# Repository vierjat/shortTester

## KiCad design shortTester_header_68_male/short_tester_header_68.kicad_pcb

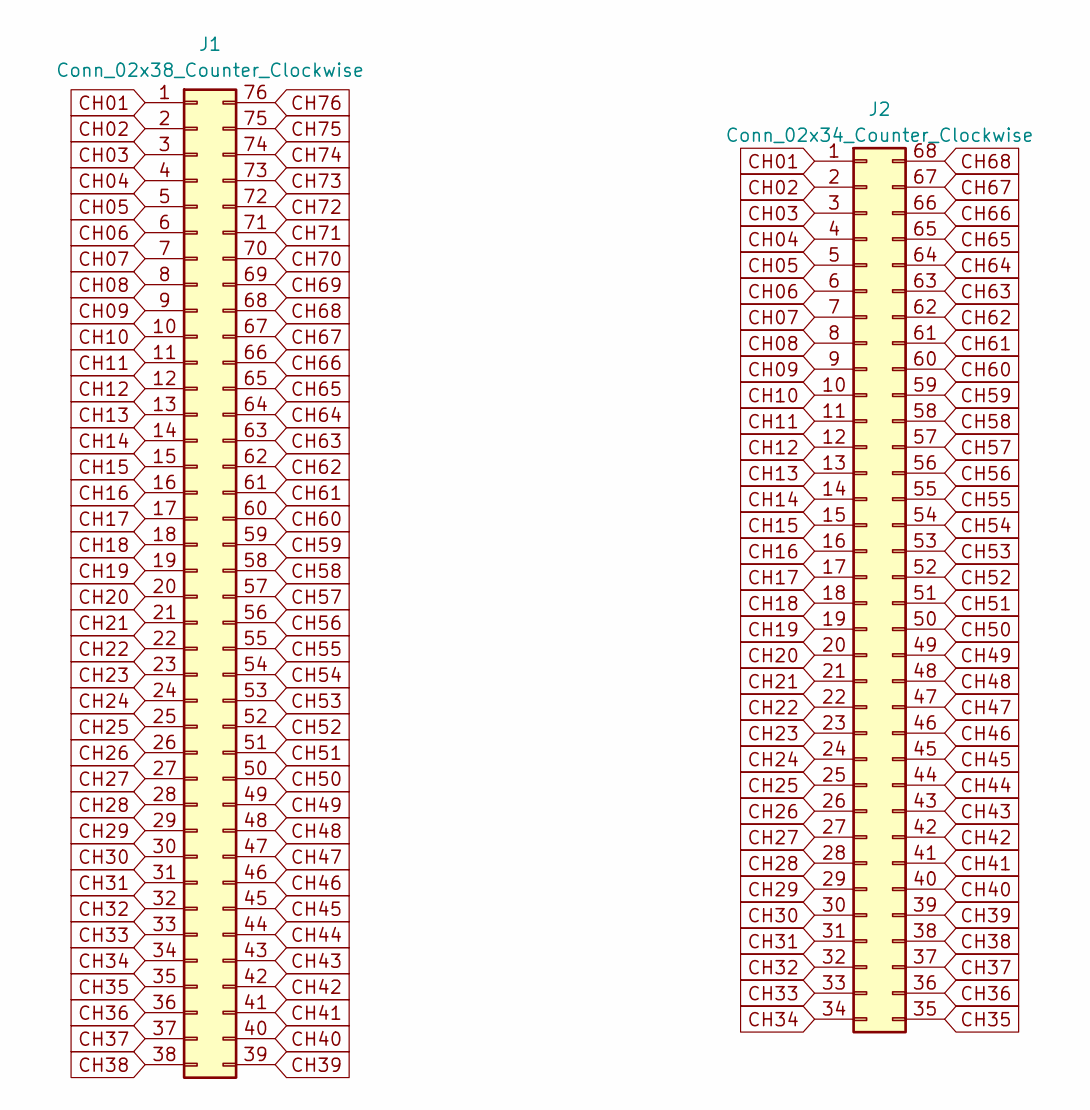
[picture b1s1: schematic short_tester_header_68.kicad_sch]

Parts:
J1: Conn_02x38_Counter_Clockwise; PinSocket_2x38_P2.54mm_Vertical
J2: Conn_02x34_Counter_Clockwise; 2-5174339-5_SSC_68pin-male

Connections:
CH01: J1.1, J2.1
CH02: J1.2, J2.2
CH03: J1.3, J2.3
CH04: J1.4, J2.4
CH05: J1.5, J2.5
CH06: J1.6, J2.6
CH07: J1.7, J2.7
CH08: J1.8, J2.8
CH09: J1.9, J2.9
CH10: J1.10, J2.10
CH11: J1.11, J2.11
CH12: J1.12, J2.12
CH13: J1.13, J2.13
CH14: J1.14, J2.14
CH15: J1.15, J2.15
CH16: J1.16, J2.16
CH17: J1.17, J2.17
CH18: J1.18, J2.18
CH19: J1.19, J2.19
CH20: J1.20, J2.20
CH21: J1.21, J2.21
CH22: J1.22, J2.22
CH23: J1.23, J2.23
CH24: J1.24, J2.24
CH25: J1.25, J2.25
CH26: J1.26, J2.26
CH27: J1.27, J2.27
CH28: J1.28, J2.28
CH29: J1.29, J2.29
CH30: J1.30, J2.30
CH31: J1.31, J2.31
CH32: J1.32, J2.32
CH33: J1.33, J2.33
CH34: J1.34, J2.34
CH35: J1.35, J2.35
CH36: J1.36, J2.36
CH37: J1.37, J2.37
CH38: J1.38, J2.38
CH39: J1.39, J2.39
CH40: J1.40, J2.40
CH41: J1.41, J2.41
CH42: J1.42, J2.42
CH43: J1.43, J2.43
CH44: J1.44, J2.44
CH45: J1.45, J2.45
CH46: J1.46, J2.46
CH47: J1.47, J2.47
CH48: J1.48, J2.48
CH49: J1.49, J2.49
CH50: J1.50, J2.50
CH51: J1.51, J2.51
CH52: J1.52, J2.52
CH53: J1.53, J2.53
CH54: J1.54, J2.54
CH55: J1.55, J2.55
CH56: J1.56, J2.56
CH57: J1.57, J2.57
CH58: J1.58, J2.58
CH59: J1.59, J2.59
CH60: J1.60, J2.60
CH61: J1.61, J2.61
CH62: J1.62, J2.62
CH63: J1.63, J2.63
CH64: J1.64, J2.64
CH65: J1.65, J2.65
CH66: J1.66, J2.66
CH67: J1.67, J2.67
CH68: J1.68, J2.68
CH69: J1.69
CH70: J1.70
CH71: J1.71
CH72: J1.72
CH73: J1.73
CH74: J1.74
CH75: J1.75
CH76: J1.76

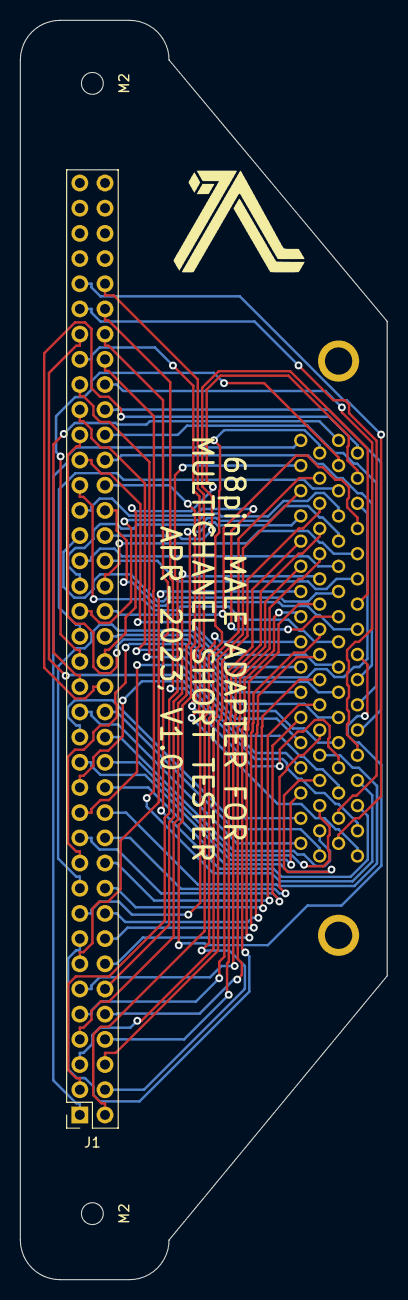
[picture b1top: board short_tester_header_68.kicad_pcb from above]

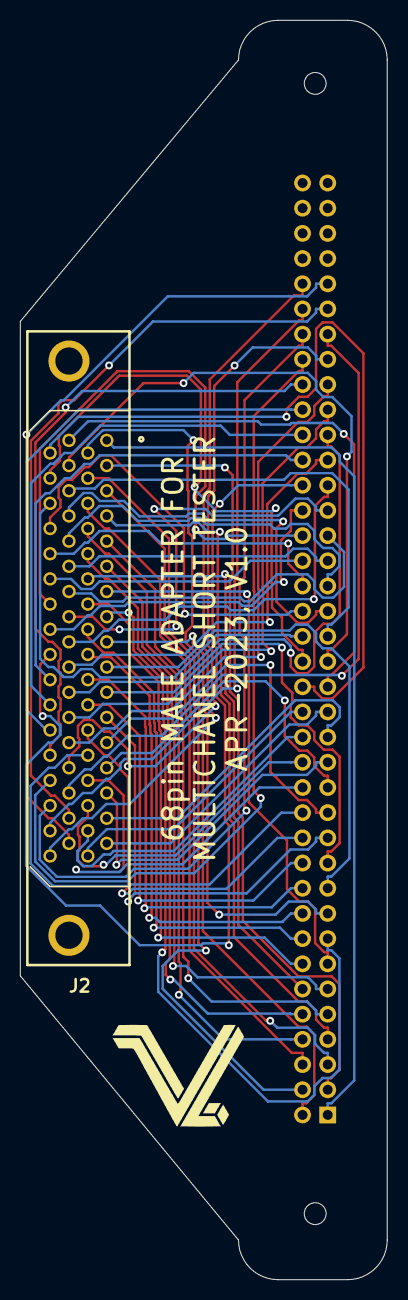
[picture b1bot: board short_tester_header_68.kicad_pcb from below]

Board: 2 copper layers, 37.0 x 127.0 mm, 6 parts (2 on the bottom side), 68 nets.

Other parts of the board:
G1, G2: LOGO; lamda15mm
M2, M2#2: MountingHole_2.2mm_M2

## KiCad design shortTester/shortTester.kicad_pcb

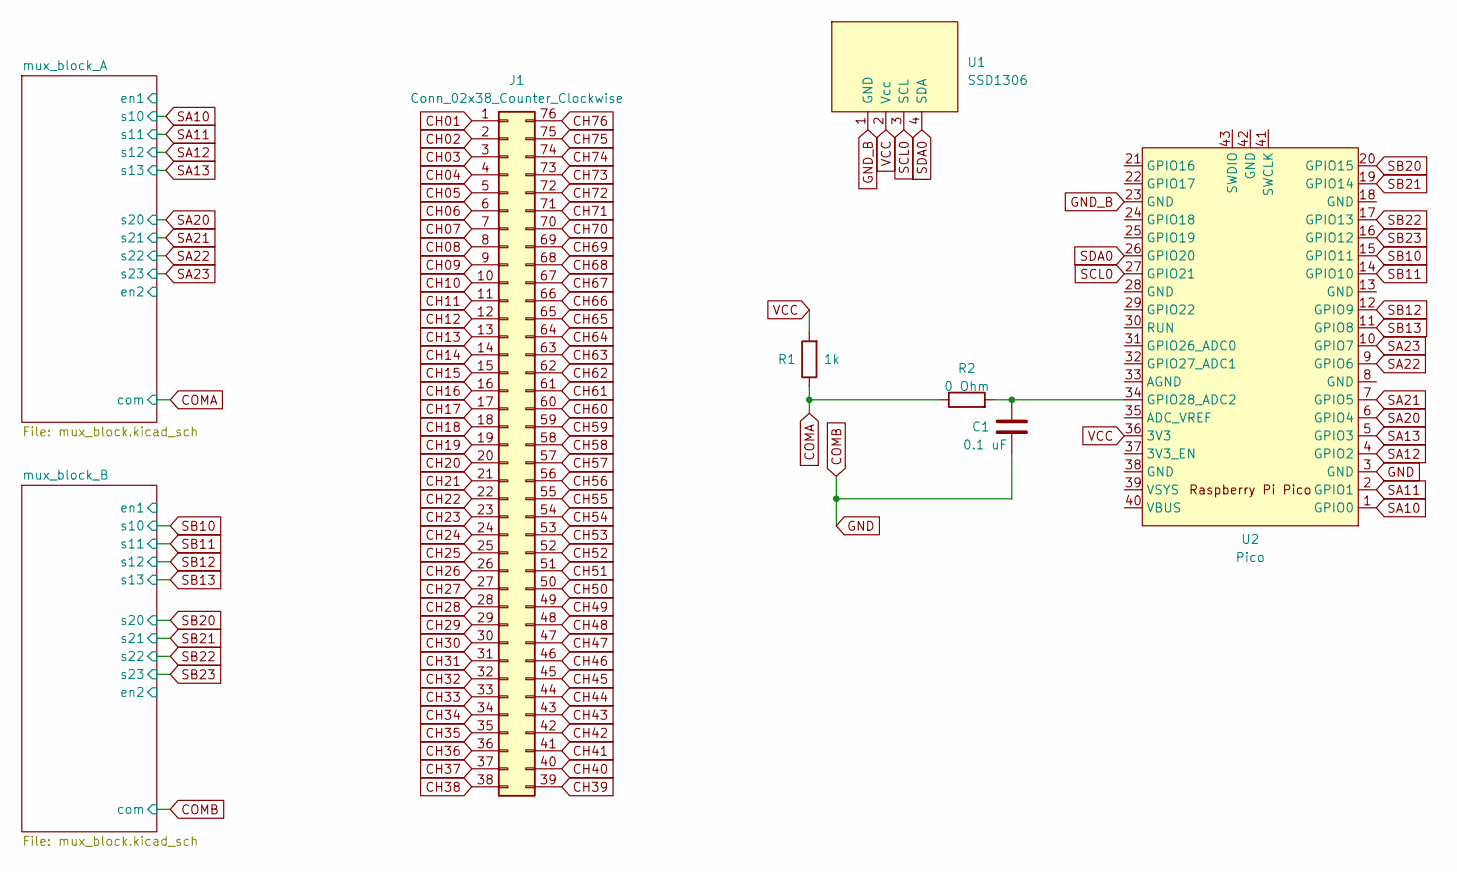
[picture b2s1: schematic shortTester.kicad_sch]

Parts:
C1: 0.1 uF; C_1210_3225Metric_Pad1.33x2.70mm_HandSolder
J1: Conn_02x38_Counter_Clockwise; PinHeader_2x38_P2.54mm_Vertical
R1: 1k; R_1210_3225Metric_Pad1.30x2.65mm_HandSolder
R2: 0 Ohm; R_1210_3225Metric_Pad1.30x2.65mm_HandSolder
U1: SSD1306
U2: Pico; RPi_Pico_SMD_TH

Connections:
CH01: J1.1; also elsewhere on the board
CH02: J1.2; also elsewhere on the board
CH03: J1.3; also elsewhere on the board
CH04: J1.4; also elsewhere on the board
CH05: J1.5; also elsewhere on the board
CH06: J1.6; also elsewhere on the board
CH07: J1.7; also elsewhere on the board
CH08: J1.8; also elsewhere on the board
CH09: J1.9; also elsewhere on the board
CH10: J1.10; also elsewhere on the board
CH11: J1.11; also elsewhere on the board
CH12: J1.12; also elsewhere on the board
CH13: J1.13; also elsewhere on the board
CH14: J1.14; also elsewhere on the board
CH15: J1.15; also elsewhere on the board
CH16: J1.16; also elsewhere on the board
CH17: J1.17; also elsewhere on the board
CH18: J1.18; also elsewhere on the board
CH19: J1.19; also elsewhere on the board
CH20: J1.20; also elsewhere on the board
CH21: J1.21; also elsewhere on the board
CH22: J1.22; also elsewhere on the board
CH23: J1.23; also elsewhere on the board
CH24: J1.24; also elsewhere on the board
CH25: J1.25; also elsewhere on the board
CH26: J1.26; also elsewhere on the board
CH27: J1.27; also elsewhere on the board
CH28: J1.28; also elsewhere on the board
CH29: J1.29; also elsewhere on the board
CH30: J1.30; also elsewhere on the board
CH31: J1.31; also elsewhere on the board
CH32: J1.32; also elsewhere on the board
CH33: J1.33; also elsewhere on the board
CH34: J1.34; also elsewhere on the board
CH35: J1.35; also elsewhere on the board
CH36: J1.36; also elsewhere on the board
CH37: J1.37; also elsewhere on the board
CH38: J1.38; also elsewhere on the board
CH39: J1.39; also elsewhere on the board
CH40: J1.40; also elsewhere on the board
CH41: J1.41; also elsewhere on the board
CH42: J1.42; also elsewhere on the board
CH43: J1.43; also elsewhere on the board
CH44: J1.44; also elsewhere on the board
CH45: J1.45; also elsewhere on the board
CH46: J1.46; also elsewhere on the board
CH47: J1.47; also elsewhere on the board
CH48: J1.48; also elsewhere on the board
CH49: J1.49; also elsewhere on the board
CH50: J1.50; also elsewhere on the board
CH51: J1.51; also elsewhere on the board
CH52: J1.52; also elsewhere on the board
CH53: J1.53; also elsewhere on the board
CH54: J1.54; also elsewhere on the board
CH55: J1.55; also elsewhere on the board
CH56: J1.56; also elsewhere on the board
CH57: J1.57; also elsewhere on the board
CH58: J1.58; also elsewhere on the board
CH59: J1.59; also elsewhere on the board
CH60: J1.60; also elsewhere on the board
CH61: J1.61; also elsewhere on the board
CH62: J1.62; also elsewhere on the board
CH63: J1.63; also elsewhere on the board
CH64: J1.64; also elsewhere on the board
CH65: J1.65; also elsewhere on the board
CH66: J1.66; also elsewhere on the board
CH67: J1.67; also elsewhere on the board
CH68: J1.68; also elsewhere on the board
CH69: J1.69; also elsewhere on the board
CH70: J1.70; also elsewhere on the board
CH71: J1.71; also elsewhere on the board
CH72: J1.72; also elsewhere on the board
CH73: J1.73; also elsewhere on the board
CH74: J1.74; also elsewhere on the board
CH75: J1.75; also elsewhere on the board
CH76: J1.76; also elsewhere on the board
COMA: R1.1, R2.1; also elsewhere on the board
COMB: C1.2, U2.3 (GND); also elsewhere on the board
GND_B: U1.1 (GND), U2.23 (GND)
unnamed: C1.1, R2.2, U2.34 (GPIO28_ADC2)
SA10: U2.1 (GPIO0); also elsewhere on the board
SA11: U2.2 (GPIO1); also elsewhere on the board
SA12: U2.4 (GPIO2); also elsewhere on the board
SA13: U2.5 (GPIO3); also elsewhere on the board
SA20: U2.6 (GPIO4); also elsewhere on the board
SA21: U2.7 (GPIO5); also elsewhere on the board
SA22: U2.9 (GPIO6); also elsewhere on the board
SA23: U2.10 (GPIO7); also elsewhere on the board
SB10: U2.15 (GPIO11); also elsewhere on the board
SB11: U2.14 (GPIO10); also elsewhere on the board
SB12: U2.12 (GPIO9); also elsewhere on the board
SB13: U2.11 (GPIO8); also elsewhere on the board
SB20: U2.20 (GPIO15); also elsewhere on the board
SB21: U2.19 (GPIO14); also elsewhere on the board
SB22: U2.17 (GPIO13); also elsewhere on the board
SB23: U2.16 (GPIO12); also elsewhere on the board
SCL0: U1.3 (SCL), U2.27 (GPIO21)
SDA0: U1.4 (SDA), U2.26 (GPIO20)
VCC: R1.2, U1.2 (Vcc), U2.36 (3V3); also elsewhere on the board

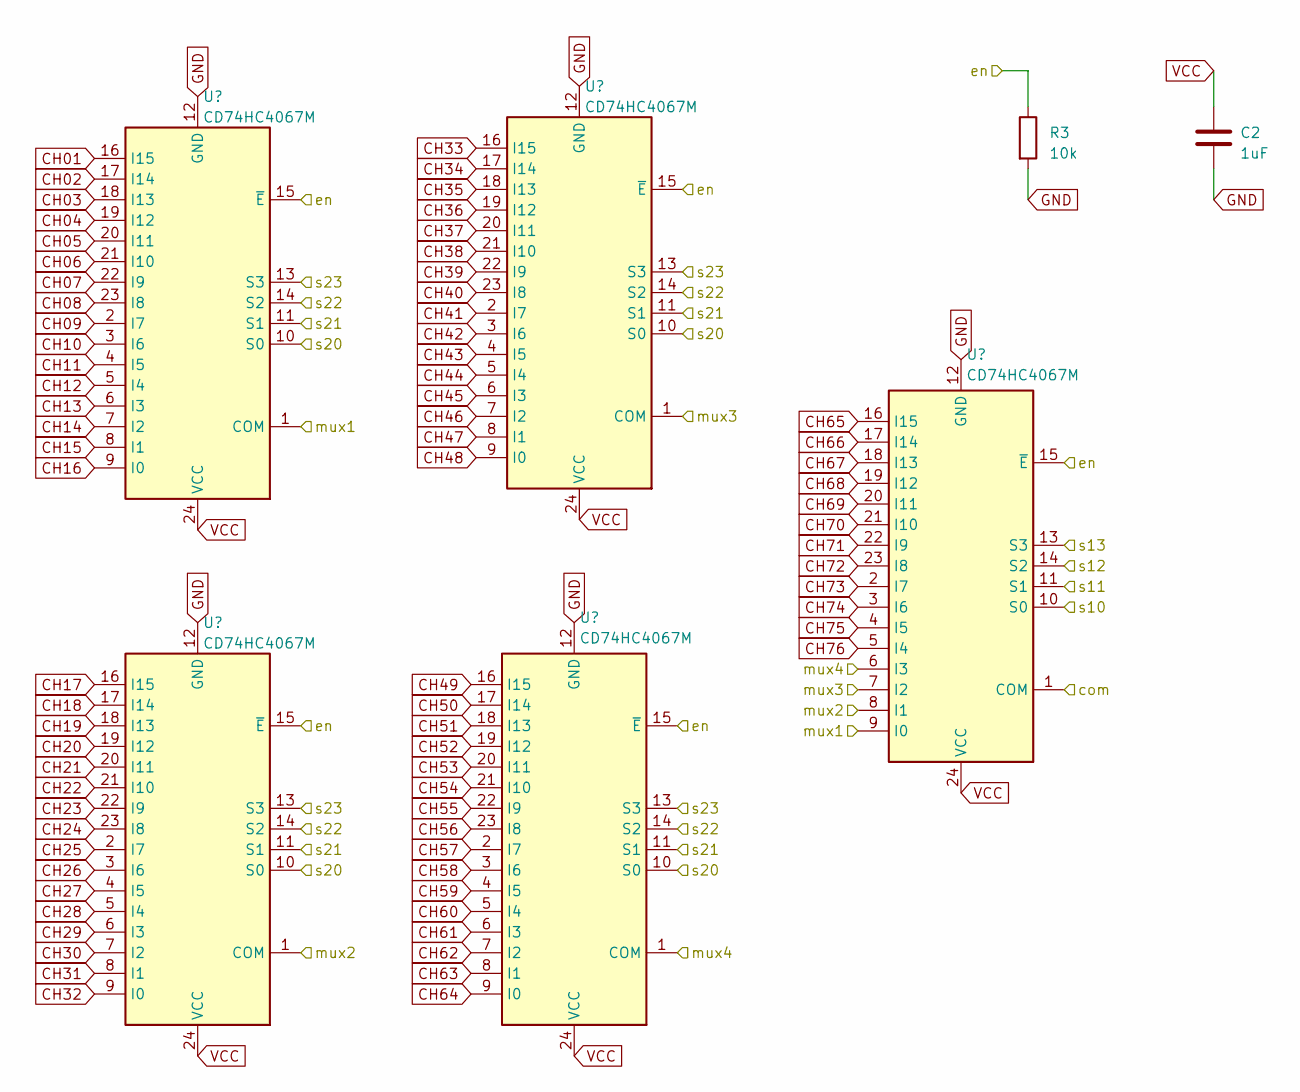
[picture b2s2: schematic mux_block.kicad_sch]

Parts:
C2: 1uF; C_1206_3216Metric_Pad1.33x1.80mm_HandSolder
R3: 10k; R_1210_3225Metric_Pad1.30x2.65mm_HandSolder
U3, U4, U5, U6, U7: CD74HC4067M; SOIC-24W_7.5x15.4mm_P1.27mm

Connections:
/mux_block_A/en: R3.1, U3.15 (~E), U4.15 (~E), U5.15 (~E), U6.15 (~E), U7.15 (~E)
/mux_block_A/mux1: U3.1 (COM), U7.9 (I0)
/mux_block_A/mux2: U4.1 (COM), U7.8 (I1)
/mux_block_A/mux3: U6.1 (COM), U7.7 (I2)
/mux_block_A/mux4: U5.1 (COM), U7.6 (I3)
CH01: U3.16 (I15); also elsewhere on the board
CH02: U3.17 (I14); also elsewhere on the board
CH03: U3.18 (I13); also elsewhere on the board
CH04: U3.19 (I12); also elsewhere on the board
CH05: U3.20 (I11); also elsewhere on the board
CH06: U3.21 (I10); also elsewhere on the board
CH07: U3.22 (I9); also elsewhere on the board
CH08: U3.23 (I8); also elsewhere on the board
CH09: U3.2 (I7); also elsewhere on the board
CH10: U3.3 (I6); also elsewhere on the board
CH11: U3.4 (I5); also elsewhere on the board
CH12: U3.5 (I4); also elsewhere on the board
CH13: U3.6 (I3); also elsewhere on the board
CH14: U3.7 (I2); also elsewhere on the board
CH15: U3.8 (I1); also elsewhere on the board
CH16: U3.9 (I0); also elsewhere on the board
CH17: U4.16 (I15); also elsewhere on the board
CH18: U4.17 (I14); also elsewhere on the board
CH19: U4.18 (I13); also elsewhere on the board
CH20: U4.19 (I12); also elsewhere on the board
CH21: U4.20 (I11); also elsewhere on the board
CH22: U4.21 (I10); also elsewhere on the board
CH23: U4.22 (I9); also elsewhere on the board
CH24: U4.23 (I8); also elsewhere on the board
CH25: U4.2 (I7); also elsewhere on the board
CH26: U4.3 (I6); also elsewhere on the board
CH27: U4.4 (I5); also elsewhere on the board
CH28: U4.5 (I4); also elsewhere on the board
CH29: U4.6 (I3); also elsewhere on the board
CH30: U4.7 (I2); also elsewhere on the board
CH31: U4.8 (I1); also elsewhere on the board
CH32: U4.9 (I0); also elsewhere on the board
CH33: U6.16 (I15); also elsewhere on the board
CH34: U6.17 (I14); also elsewhere on the board
CH35: U6.18 (I13); also elsewhere on the board
CH36: U6.19 (I12); also elsewhere on the board
CH37: U6.20 (I11); also elsewhere on the board
CH38: U6.21 (I10); also elsewhere on the board
CH39: U6.22 (I9); also elsewhere on the board
CH40: U6.23 (I8); also elsewhere on the board
CH41: U6.2 (I7); also elsewhere on the board
CH42: U6.3 (I6); also elsewhere on the board
CH43: U6.4 (I5); also elsewhere on the board
CH44: U6.5 (I4); also elsewhere on the board
CH45: U6.6 (I3); also elsewhere on the board
CH46: U6.7 (I2); also elsewhere on the board
CH47: U6.8 (I1); also elsewhere on the board
CH48: U6.9 (I0); also elsewhere on the board
CH49: U5.16 (I15); also elsewhere on the board
CH50: U5.17 (I14); also elsewhere on the board
CH51: U5.18 (I13); also elsewhere on the board
CH52: U5.19 (I12); also elsewhere on the board
CH53: U5.20 (I11); also elsewhere on the board
CH54: U5.21 (I10); also elsewhere on the board
CH55: U5.22 (I9); also elsewhere on the board
CH56: U5.23 (I8); also elsewhere on the board
CH57: U5.2 (I7); also elsewhere on the board
CH58: U5.3 (I6); also elsewhere on the board
CH59: U5.4 (I5); also elsewhere on the board
CH60: U5.5 (I4); also elsewhere on the board
CH61: U5.6 (I3); also elsewhere on the board
CH62: U5.7 (I2); also elsewhere on the board
CH63: U5.8 (I1); also elsewhere on the board
CH64: U5.9 (I0); also elsewhere on the board
CH65: U7.16 (I15); also elsewhere on the board
CH66: U7.17 (I14); also elsewhere on the board
CH67: U7.18 (I13); also elsewhere on the board
CH68: U7.19 (I12); also elsewhere on the board
CH69: U7.20 (I11); also elsewhere on the board
CH70: U7.21 (I10); also elsewhere on the board
CH71: U7.22 (I9); also elsewhere on the board
CH72: U7.23 (I8); also elsewhere on the board
CH73: U7.2 (I7); also elsewhere on the board
CH74: U7.3 (I6); also elsewhere on the board
CH75: U7.4 (I5); also elsewhere on the board
CH76: U7.5 (I4); also elsewhere on the board
COMA: U7.1 (COM); also elsewhere on the board
COMB: C2.2, R3.2, U3.12 (GND), U4.12 (GND), U5.12 (GND), U6.12 (GND), U7.12 (GND); also elsewhere on the board
SA10: U7.10 (S0); also elsewhere on the board
SA11: U7.11 (S1); also elsewhere on the board
SA12: U7.14 (S2); also elsewhere on the board
SA13: U7.13 (S3); also elsewhere on the board
SA20: U3.10 (S0), U4.10 (S0), U5.10 (S0), U6.10 (S0); also elsewhere on the board
SA21: U3.11 (S1), U4.11 (S1), U5.11 (S1), U6.11 (S1); also elsewhere on the board
SA22: U3.14 (S2), U4.14 (S2), U5.14 (S2), U6.14 (S2); also elsewhere on the board
SA23: U3.13 (S3), U4.13 (S3), U5.13 (S3), U6.13 (S3); also elsewhere on the board
VCC: C2.1, U3.24 (VCC), U4.24 (VCC), U5.24 (VCC), U6.24 (VCC), U7.24 (VCC); also elsewhere on the board

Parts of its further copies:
C3: 1uF; C_1206_3216Metric_Pad1.33x1.80mm_HandSolder
R4: 10k; R_1210_3225Metric_Pad1.30x2.65mm_HandSolder
U8, U9, U10, U11, U12: CD74HC4067M; SOIC-24W_7.5x15.4mm_P1.27mm

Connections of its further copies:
/mux_block_B/en: R4.1, U8.15 (~E), U9.15 (~E), U10.15 (~E), U11.15 (~E), U12.15 (~E)
/mux_block_B/mux1: U8.1 (COM), U12.9 (I0)
/mux_block_B/mux2: U9.1 (COM), U12.8 (I1)
/mux_block_B/mux3: U11.1 (COM), U12.7 (I2)
/mux_block_B/mux4: U10.1 (COM), U12.6 (I3)
CH01: U8.16 (I15); also elsewhere on the board
CH02: U8.17 (I14); also elsewhere on the board
CH03: U8.18 (I13); also elsewhere on the board
CH04: U8.19 (I12); also elsewhere on the board
CH05: U8.20 (I11); also elsewhere on the board
CH06: U8.21 (I10); also elsewhere on the board
CH07: U8.22 (I9); also elsewhere on the board
CH08: U8.23 (I8); also elsewhere on the board
CH09: U8.2 (I7); also elsewhere on the board
CH10: U8.3 (I6); also elsewhere on the board
CH11: U8.4 (I5); also elsewhere on the board
CH12: U8.5 (I4); also elsewhere on the board
CH13: U8.6 (I3); also elsewhere on the board
CH14: U8.7 (I2); also elsewhere on the board
CH15: U8.8 (I1); also elsewhere on the board
CH16: U8.9 (I0); also elsewhere on the board
CH17: U9.16 (I15); also elsewhere on the board
CH18: U9.17 (I14); also elsewhere on the board
CH19: U9.18 (I13); also elsewhere on the board
CH20: U9.19 (I12); also elsewhere on the board
CH21: U9.20 (I11); also elsewhere on the board
CH22: U9.21 (I10); also elsewhere on the board
CH23: U9.22 (I9); also elsewhere on the board
CH24: U9.23 (I8); also elsewhere on the board
CH25: U9.2 (I7); also elsewhere on the board
CH26: U9.3 (I6); also elsewhere on the board
CH27: U9.4 (I5); also elsewhere on the board
CH28: U9.5 (I4); also elsewhere on the board
CH29: U9.6 (I3); also elsewhere on the board
CH30: U9.7 (I2); also elsewhere on the board
CH31: U9.8 (I1); also elsewhere on the board
CH32: U9.9 (I0); also elsewhere on the board
CH33: U11.16 (I15); also elsewhere on the board
CH34: U11.17 (I14); also elsewhere on the board
CH35: U11.18 (I13); also elsewhere on the board
CH36: U11.19 (I12); also elsewhere on the board
CH37: U11.20 (I11); also elsewhere on the board
CH38: U11.21 (I10); also elsewhere on the board
CH39: U11.22 (I9); also elsewhere on the board
CH40: U11.23 (I8); also elsewhere on the board
CH41: U11.2 (I7); also elsewhere on the board
CH42: U11.3 (I6); also elsewhere on the board
CH43: U11.4 (I5); also elsewhere on the board
CH44: U11.5 (I4); also elsewhere on the board
CH45: U11.6 (I3); also elsewhere on the board
CH46: U11.7 (I2); also elsewhere on the board
CH47: U11.8 (I1); also elsewhere on the board
CH48: U11.9 (I0); also elsewhere on the board
CH49: U10.16 (I15); also elsewhere on the board
CH50: U10.17 (I14); also elsewhere on the board
CH51: U10.18 (I13); also elsewhere on the board
CH52: U10.19 (I12); also elsewhere on the board
CH53: U10.20 (I11); also elsewhere on the board
CH54: U10.21 (I10); also elsewhere on the board
CH55: U10.22 (I9); also elsewhere on the board
CH56: U10.23 (I8); also elsewhere on the board
CH57: U10.2 (I7); also elsewhere on the board
CH58: U10.3 (I6); also elsewhere on the board
CH59: U10.4 (I5); also elsewhere on the board
CH60: U10.5 (I4); also elsewhere on the board
CH61: U10.6 (I3); also elsewhere on the board
CH62: U10.7 (I2); also elsewhere on the board
CH63: U10.8 (I1); also elsewhere on the board
CH64: U10.9 (I0); also elsewhere on the board
CH65: U12.16 (I15); also elsewhere on the board
CH66: U12.17 (I14); also elsewhere on the board
CH67: U12.18 (I13); also elsewhere on the board
CH68: U12.19 (I12); also elsewhere on the board
CH69: U12.20 (I11); also elsewhere on the board
CH70: U12.21 (I10); also elsewhere on the board
CH71: U12.22 (I9); also elsewhere on the board
CH72: U12.23 (I8); also elsewhere on the board
CH73: U12.2 (I7); also elsewhere on the board
CH74: U12.3 (I6); also elsewhere on the board
CH75: U12.4 (I5); also elsewhere on the board
CH76: U12.5 (I4); also elsewhere on the board
COMB: C3.2, R4.2, U8.12 (GND), U9.12 (GND), U10.12 (GND), U11.12 (GND), U12.1 (COM), U12.12 (GND); also elsewhere on the board
SB10: U12.10 (S0); also elsewhere on the board
SB11: U12.11 (S1); also elsewhere on the board
SB12: U12.14 (S2); also elsewhere on the board
SB13: U12.13 (S3); also elsewhere on the board
SB20: U8.10 (S0), U9.10 (S0), U10.10 (S0), U11.10 (S0); also elsewhere on the board
SB21: U8.11 (S1), U9.11 (S1), U10.11 (S1), U11.11 (S1); also elsewhere on the board
SB22: U8.14 (S2), U9.14 (S2), U10.14 (S2), U11.14 (S2); also elsewhere on the board
SB23: U8.13 (S3), U9.13 (S3), U10.13 (S3), U11.13 (S3); also elsewhere on the board
VCC: C3.1, U8.24 (VCC), U9.24 (VCC), U10.24 (VCC), U11.24 (VCC), U12.24 (VCC); also elsewhere on the board

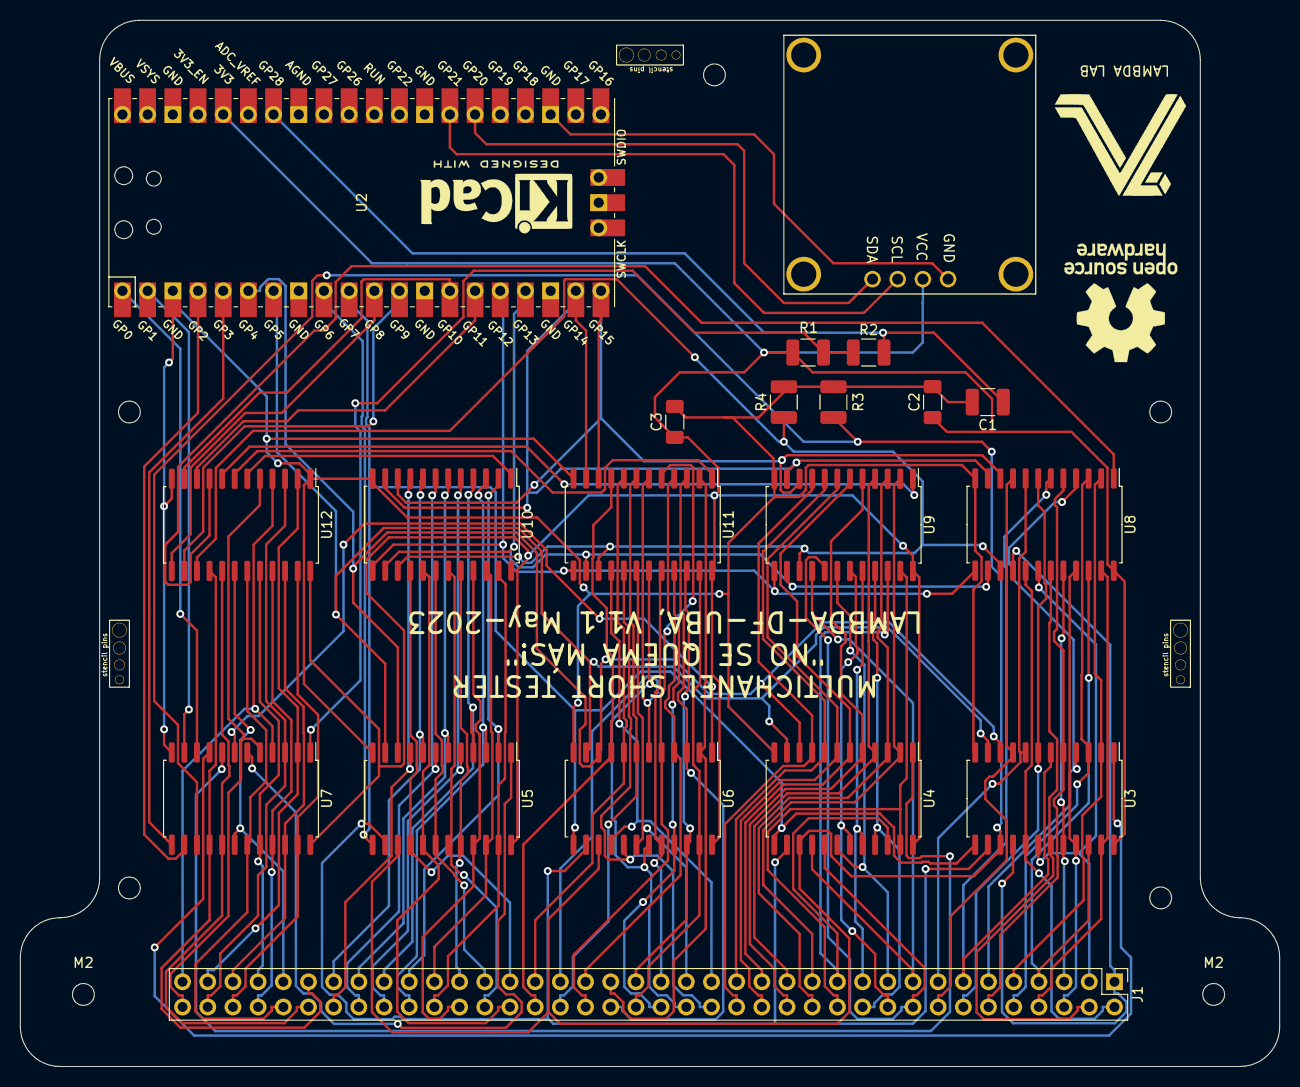
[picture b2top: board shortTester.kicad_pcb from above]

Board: 2 copper layers, 127.0 x 105.5 mm, 27 parts (0 on the bottom side), 109 nets.

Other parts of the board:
M2, M2#2, M2#3, M2#4, M2#5, M2#6, M2#7: MountingHole_2.2mm_M2

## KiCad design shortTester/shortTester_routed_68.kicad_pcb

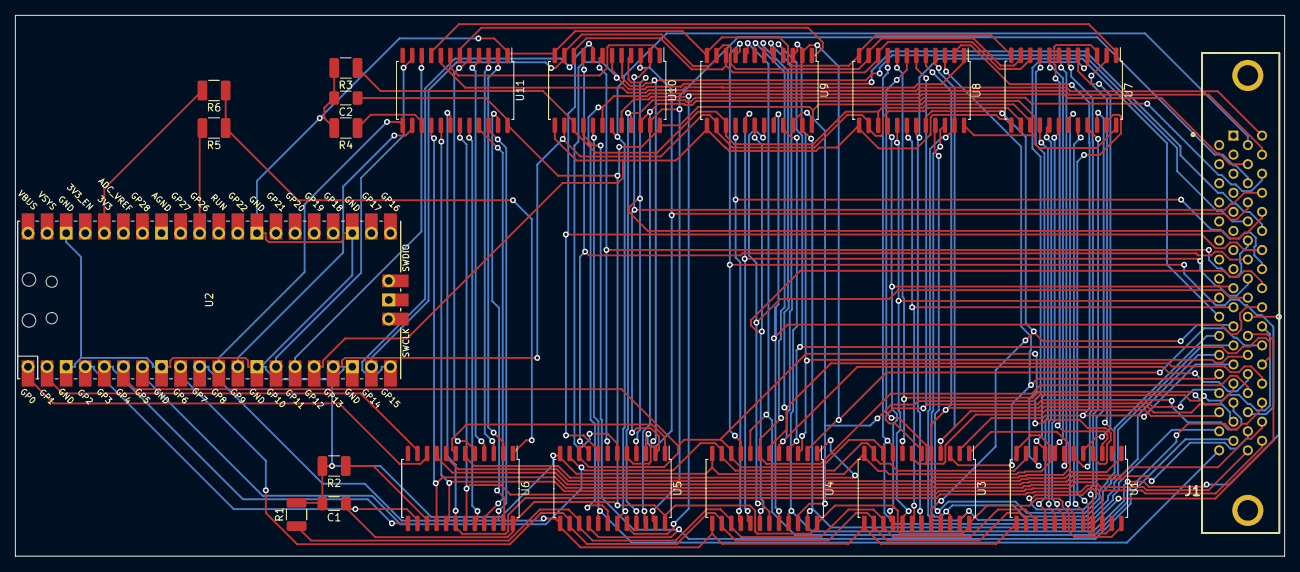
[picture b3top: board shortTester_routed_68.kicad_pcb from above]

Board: 2 copper layers, 169.0 x 72.0 mm, 20 parts (0 on the bottom side), 109 nets.

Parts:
C1, C2: 1uF; C_1206_3216Metric_Pad1.33x1.80mm_HandSolder
J1: Conn_02x34_Counter_Clockwise; 2-5787394-7_SSC_68pin_RighAngleFemale
R1, R2, R3, R4: 10k; R_1210_3225Metric_Pad1.30x2.65mm_HandSolder
R5: R; R_1210_3225Metric_Pad1.30x2.65mm_HandSolder
R6: 1k; R_1210_3225Metric_Pad1.30x2.65mm_HandSolder
U1, U3, U4, U5, U6, U7, U8, U9, U10, U11: CD74HC4067M; SOIC-24W_7.5x15.4mm_P1.27mm
U2: Pico; RPi_Pico_SMD_TH

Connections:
/mux_block_A/en1: R2.1, U6.15 (~E)
/mux_block_A/en2: R1.1, U1.15 (~E), U3.15 (~E), U4.15 (~E), U5.15 (~E)
/mux_block_A/mux1: U1.1 (COM), U6.9 (I0)
/mux_block_A/mux2: U3.1 (COM), U6.8 (I1)
/mux_block_A/mux3: U5.1 (COM), U6.7 (I2)
/mux_block_A/mux4: U4.1 (COM), U6.6 (I3)
/mux_block_B/en1: R4.1, U11.15 (~E)
/mux_block_B/en2: R3.1, U7.15 (~E), U8.15 (~E), U9.15 (~E), U10.15 (~E)
/mux_block_B/mux1: U7.1 (COM), U11.9 (I0)
/mux_block_B/mux2: U8.1 (COM), U11.8 (I1)
/mux_block_B/mux3: U10.1 (COM), U11.7 (I2)
/mux_block_B/mux4: U9.1 (COM), U11.6 (I3)
CH17: J1.17, U3.16 (I15), U8.16 (I15)
CH18: J1.18, U3.17 (I14), U8.17 (I14)
CH19: J1.19, U3.18 (I13), U8.18 (I13)
CH20: J1.20, U3.19 (I12), U8.19 (I12)
CH21: J1.21, U3.20 (I11), U8.20 (I11)
CH22: J1.22, U3.21 (I10), U8.21 (I10)
CH23: J1.23, U3.22 (I9), U8.22 (I9)
CH24: J1.24, U3.23 (I8), U8.23 (I8)
CH25: J1.25, U3.2 (I7), U8.2 (I7)
CH26: J1.26, U3.3 (I6), U8.3 (I6)
CH27: J1.27, U3.4 (I5), U8.4 (I5)
CH28: J1.28, U3.5 (I4), U8.5 (I4)
CH29: J1.29, U3.6 (I3), U8.6 (I3)
CH30: J1.30, U3.7 (I2), U8.7 (I2)
CH31: J1.31, U3.8 (I1), U8.8 (I1)
CH32: J1.32, U3.9 (I0), U8.9 (I0)
CH33: J1.33, U5.16 (I15), U10.16 (I15)
CH34: J1.34, U5.17 (I14), U10.17 (I14)
CH35: J1.35, U5.18 (I13), U10.18 (I13)
CH36: J1.36, U5.19 (I12), U10.19 (I12)
CH37: J1.37, U5.20 (I11), U10.20 (I11)
CH38: J1.38, U5.21 (I10), U10.21 (I10)
CH39: J1.39, U5.22 (I9), U10.22 (I9)
CH40: J1.40, U5.23 (I8), U10.23 (I8)
CH41: J1.41, U5.2 (I7), U10.2 (I7)
CH42: J1.42, U5.3 (I6), U10.3 (I6)
CH43: J1.43, U5.4 (I5), U10.4 (I5)
CH44: J1.44, U5.5 (I4), U10.5 (I4)
CH45: J1.45, U5.6 (I3), U10.6 (I3)
CH46: J1.46, U5.7 (I2), U10.7 (I2)
CH47: J1.47, U5.8 (I1), U10.8 (I1)
CH48: J1.48, U5.9 (I0), U10.9 (I0)
CH49: J1.49, U4.16 (I15), U9.16 (I15)
CH50: J1.50, U4.17 (I14), U9.17 (I14)
CH51: J1.51, U4.18 (I13), U9.18 (I13)
CH52: J1.52, U4.19 (I12), U9.19 (I12)
CH53: J1.53, U4.20 (I11), U9.20 (I11)
CH54: J1.54, U4.21 (I10), U9.21 (I10)
CH55: J1.55, U4.22 (I9), U9.22 (I9)
CH56: J1.56, U4.23 (I8), U9.23 (I8)
CH57: J1.57, U4.2 (I7), U9.2 (I7)
CH58: J1.58, U4.3 (I6), U9.3 (I6)
CH59: J1.59, U4.4 (I5), U9.4 (I5)
CH60: J1.60, U4.5 (I4), U9.5 (I4)
CH61: J1.61, U4.6 (I3), U9.6 (I3)
CH62: J1.62, U4.7 (I2), U9.7 (I2)
CH63: J1.63, U4.8 (I1), U9.8 (I1)
CH64: J1.64, U4.9 (I0), U9.9 (I0)
CH65: J1.65, U6.16 (I15), U11.16 (I15)
CH66: J1.66, U6.17 (I14), U11.17 (I14)
CH67: J1.67, U6.18 (I13), U11.18 (I13)
CH68: J1.68, U6.19 (I12), U11.19 (I12)
CH69: U6.20 (I11), U11.20 (I11)
CH70: U6.21 (I10), U11.21 (I10)
CH71: U6.22 (I9), U11.22 (I9)
CH72: U6.23 (I8), U11.23 (I8)
CH73: U6.2 (I7), U11.2 (I7)
CH74: U6.3 (I6), U11.3 (I6)
CH75: U6.4 (I5), U11.4 (I5)
CH76: U6.5 (I4), U11.5 (I4)
CH_01: U1.16 (I15), U7.16 (I15)
CH_02: U1.17 (I14), U7.17 (I14)
CH_03: U1.18 (I13), U7.18 (I13)
CH_04: U1.19 (I12), U7.19 (I12)
CH_05: U1.20 (I11), U7.20 (I11)
CH_06: U1.21 (I10), U7.21 (I10)
CH_07: U1.22 (I9), U7.22 (I9)
CH_08: U1.23 (I8), U7.23 (I8)
CH_09: U1.2 (I7), U7.2 (I7)
CH_10: U1.3 (I6), U7.3 (I6)
CH_11: U1.4 (I5), U7.4 (I5)
CH_12: U1.5 (I4), U7.5 (I4)
CH_13: U1.6 (I3), U7.6 (I3)
CH_14: U1.7 (I2), U7.7 (I2)
CH_15: U1.8 (I1), U7.8 (I1)
CH_16: U1.9 (I0), U7.9 (I0)
COMA: R5.1, R6.1, U6.1 (COM)
COMB: C1.2, C2.2, R1.2, R2.2, R3.2, R4.2, U1.12 (GND), U2.3 (GND), U2.8 (GND), U2.13 (GND), U2.18 (GND), U2.23 (GND), U2.28 (GND), U2.38 (GND), U3.12 (GND), U4.12 (GND), U5.12 (GND), U7.12 (GND), U8.12 (GND), U9.12 (GND), U10.12 (GND), U11.1 (COM)
unnamed: R5.2, U2.31 (GPIO26_ADC0)
SA10: U2.1 (GPIO0), U6.10 (S0)
SA11: U2.2 (GPIO1), U6.11 (S1)
SA12: U2.4 (GPIO2), U6.14 (S2)
SA13: U2.5 (GPIO3), U6.13 (S3)
SA20: U1.10 (S0), U2.6 (GPIO4), U3.10 (S0), U4.10 (S0), U5.10 (S0)
SA21: U1.11 (S1), U2.7 (GPIO5), U3.11 (S1), U4.11 (S1), U5.11 (S1)
SA22: U1.14 (S2), U2.9 (GPIO6), U3.14 (S2), U4.14 (S2), U5.14 (S2)
SA23: U1.13 (S3), U2.10 (GPIO7), U3.13 (S3), U4.13 (S3), U5.13 (S3)
SB10: U2.15 (GPIO11), U11.10 (S0)
SB11: U2.14 (GPIO10), U11.11 (S1)
SB12: U2.12 (GPIO9), U11.14 (S2)
SB13: U2.11 (GPIO8), U11.13 (S3)
SB20: U2.20 (GPIO15), U7.10 (S0), U8.10 (S0), U9.10 (S0), U10.10 (S0)
SB21: U2.19 (GPIO14), U7.11 (S1), U8.11 (S1), U9.11 (S1), U10.11 (S1)
SB22: U2.17 (GPIO13), U7.14 (S2), U8.14 (S2), U9.14 (S2), U10.14 (S2)
SB23: U2.16 (GPIO12), U7.13 (S3), U8.13 (S3), U9.13 (S3), U10.13 (S3)
VCC: C1.1, C2.1, U1.24 (VCC), U3.24 (VCC), U4.24 (VCC), U5.24 (VCC), U6.24 (VCC), U7.24 (VCC), U8.24 (VCC), U9.24 (VCC), U10.24 (VCC), U11.24 (VCC)
VDD: R6.2, U2.36 (3V3)

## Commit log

2023-07-05 Fixed missing tracks. Simplified MUx GND. Added software.
